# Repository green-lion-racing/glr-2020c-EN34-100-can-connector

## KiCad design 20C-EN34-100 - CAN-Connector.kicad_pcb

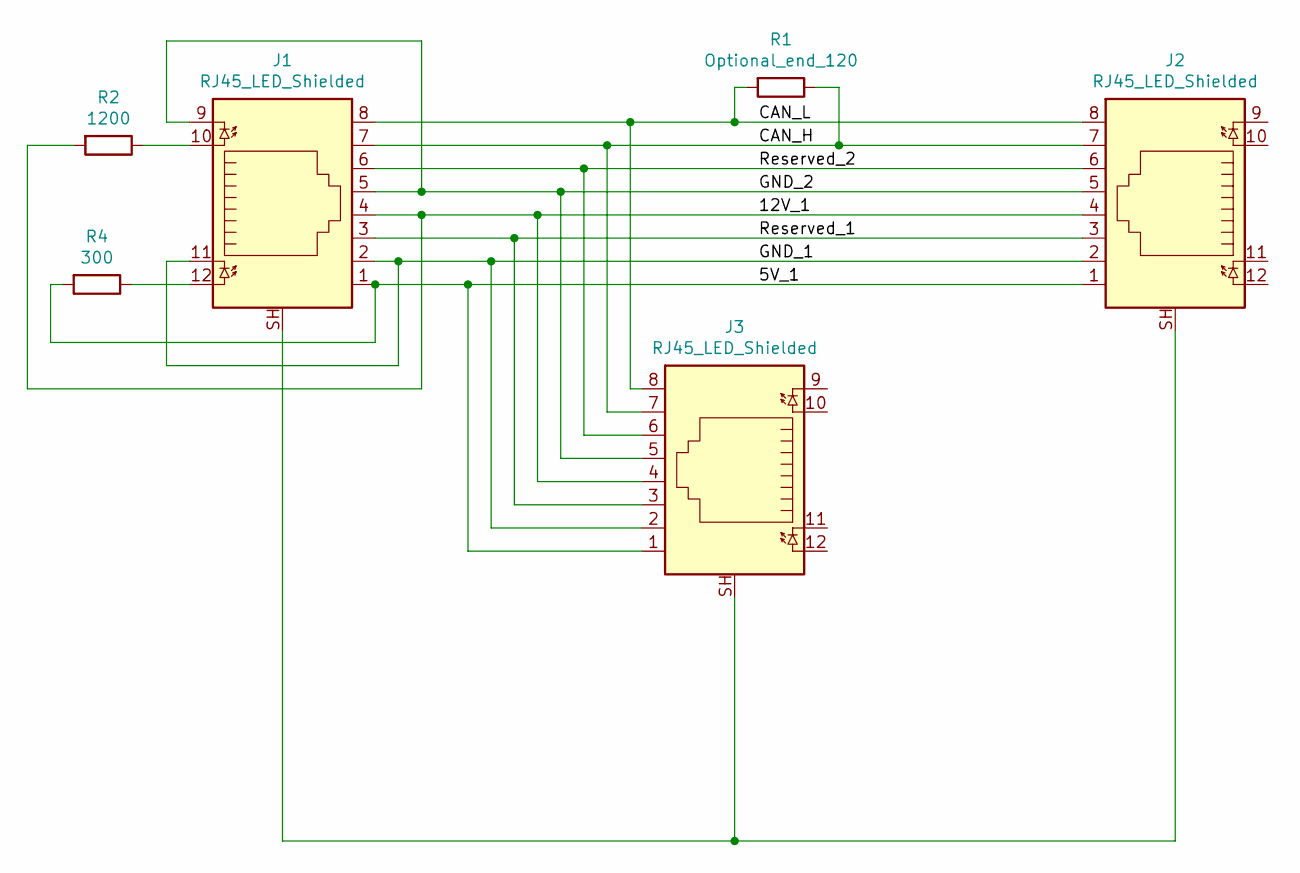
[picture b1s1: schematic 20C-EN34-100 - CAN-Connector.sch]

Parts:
J1, J2, J3: RJ45_LED_Shielded; RJ45_Female_TE_6116173-4
R1: Optional_end_120; R_0603_1608Metric_Pad1.05x0.95mm_HandSolder
R2: 1200; R_0603_1608Metric_Pad1.05x0.95mm_HandSolder
R4: 300; R_0603_1608Metric_Pad1.05x0.95mm_HandSolder

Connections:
/5V_1: J1.1, J2.1, J3.1, R4.2
/12V_1: J1.4, J2.4, J3.4, R2.2
/CAN_H: J1.7, J2.7, J3.7, R1.1
/CAN_L: J1.8, J2.8, J3.8, R1.2
/GND_1: J1.2, J1.11, J2.2, J3.2
/GND_2: J1.5, J1.9, J2.5, J3.5
/Reserved_1: J1.3, J2.3, J3.3
/Reserved_2: J1.6, J2.6, J3.6
unnamed: J1.10, R2.1
unnamed: J1.12, R4.1
unnamed: J1.SH, J2.SH, J3.SH

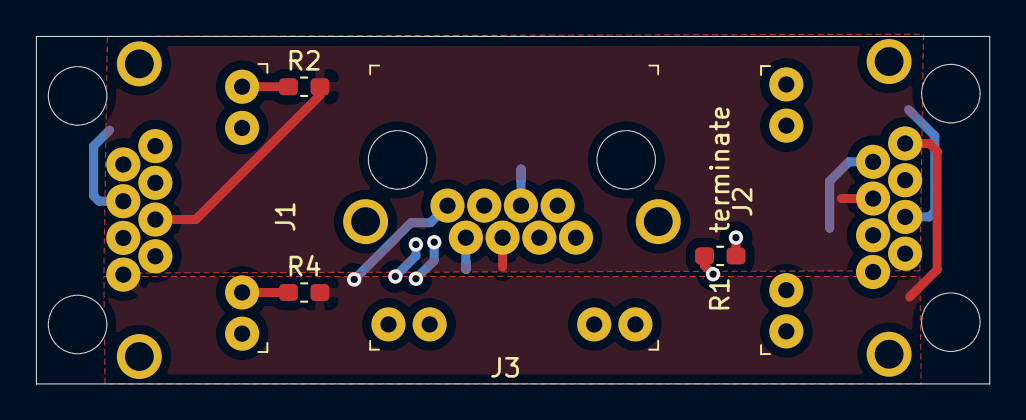
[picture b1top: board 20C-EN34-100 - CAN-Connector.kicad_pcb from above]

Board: 4 copper layers, 53.0 x 19.3 mm, 6 parts (0 on the bottom side), 11 nets.

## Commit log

2020-01-21 V01 - initial commit
    created project
2023-12-01 Create LICENSE
